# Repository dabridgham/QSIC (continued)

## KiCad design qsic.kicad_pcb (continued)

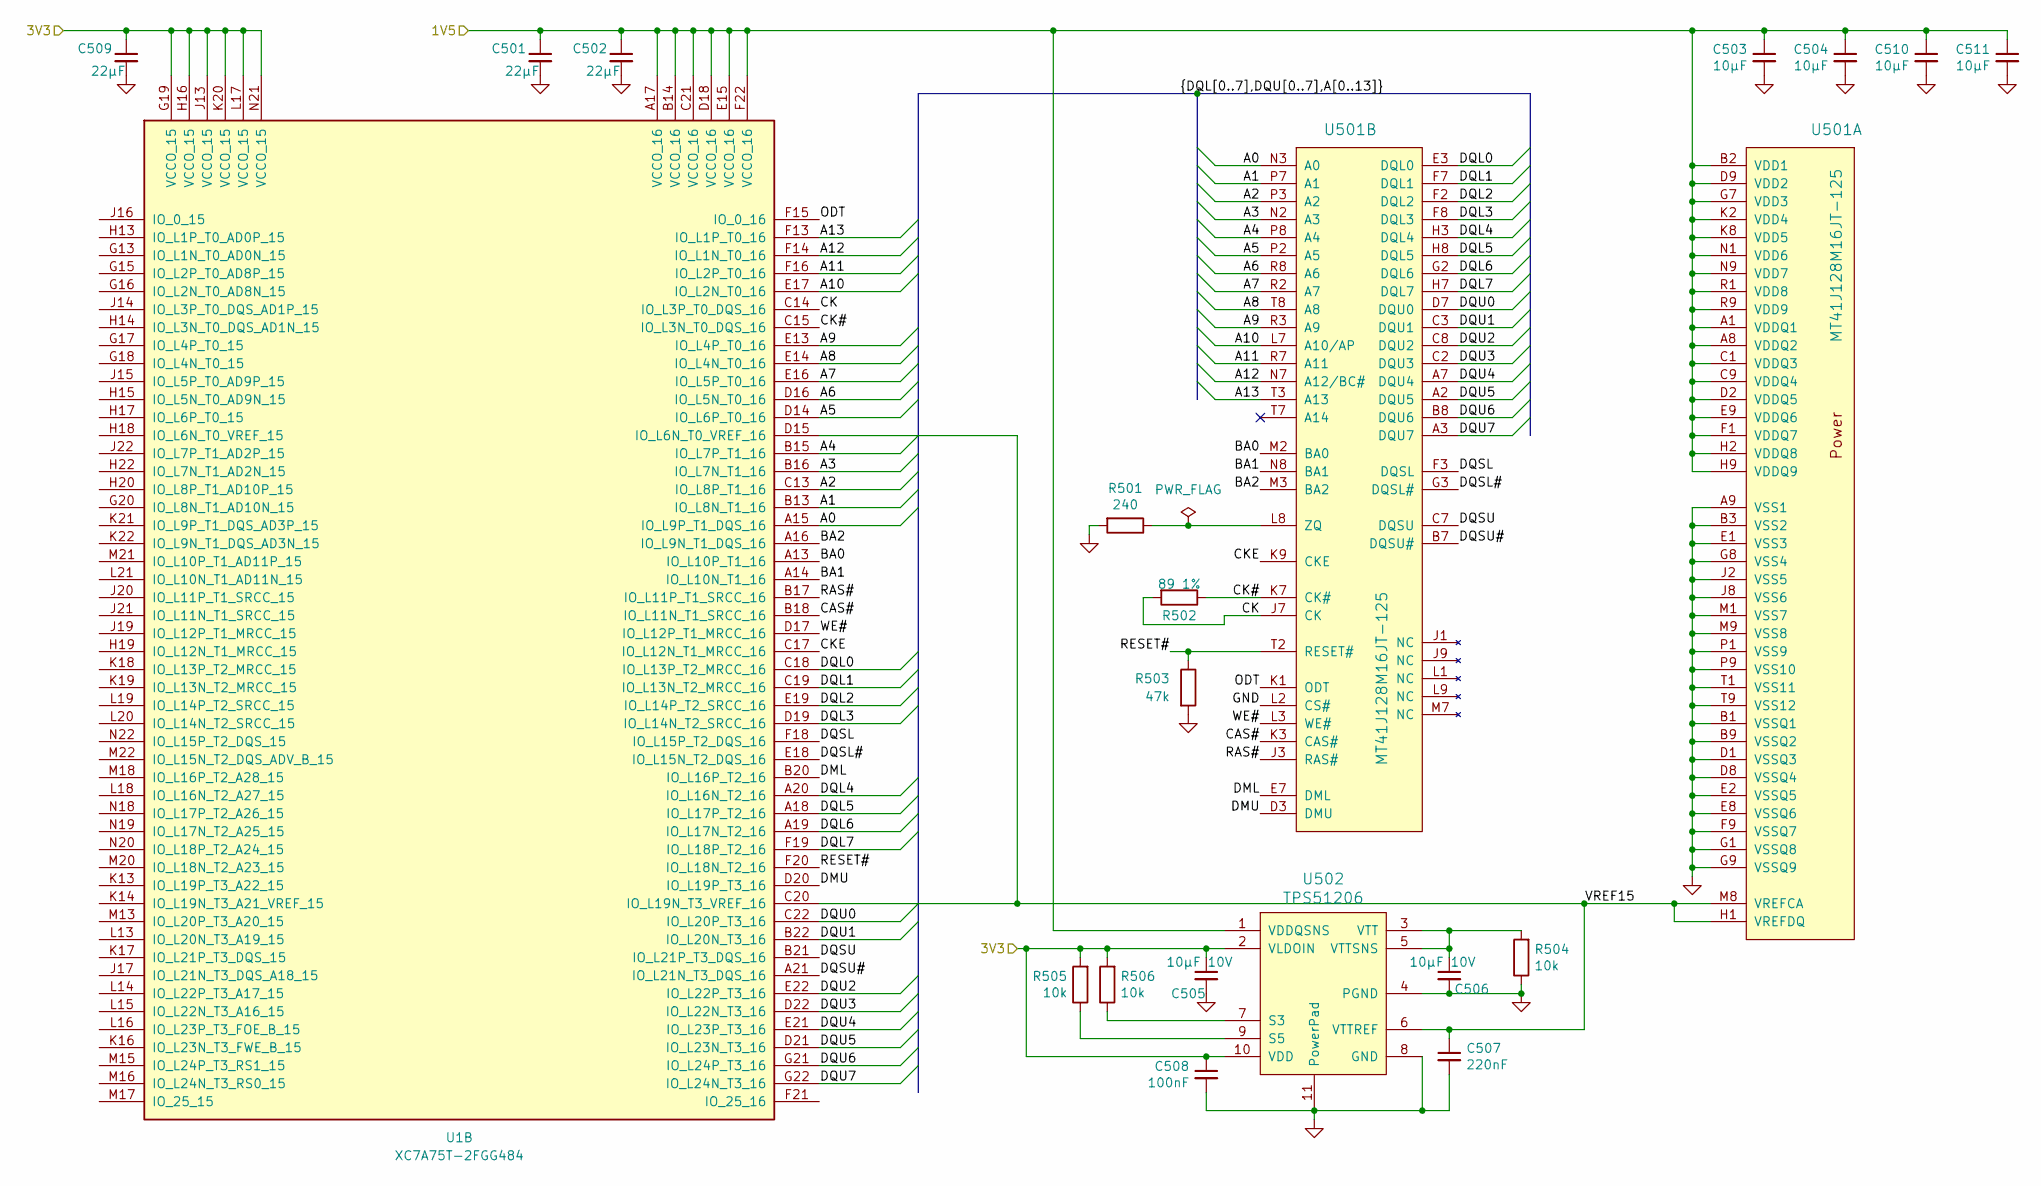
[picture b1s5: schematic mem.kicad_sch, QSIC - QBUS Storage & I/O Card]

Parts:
C501, C502, C509: 22µF; C_0603_1608Metric; MPN CL10A226MP8NUNE; JLCPCB Part C59461
C503, C504, C510, C511: 10µF; C_0603_1608Metric; MPN CL10A106MP8NNNC; JLCPCB Part C85713
C505, C506: 10µF 10V; C_0603_1608Metric; MPN CL10A106MP8NNNC; JLCPCB Part C85713
C507: 220nF; C_0603_1608Metric; MPN CL10B224KO8NNNC
C508: 100nF; C_0603_1608Metric; MPN CL10B104KO8NNNC
R501: 240; R_0603_1608Metric; MPN RC0603FR-07240RL
R502: 89 1%; R_0603_1608Metric; MPN RC0603FR-0788R7L; JLCPCB Part C273787
R503: 47k; R_0603_1608Metric; MPN RC0603FR-0747KL
R504, R505, R506: 10k; R_0603_1608Metric; MPN RC0603FR-0710KL
U1: XC7A75T-2FGG484; Xilinx_FGG484
U501: MT41J128M16JT-125; BGA-96_9.0x13.0mm_Layout2x3x16_P0.8mm; MPN MT41J128M16JT-125:K TR
U502: TPS51206; WSON-10-1EP_2x2mm_P0.4mm_EP0.9x1.5mm_ThermalVias; MPN TPS51206DSQR; JLCPCB Part C88038

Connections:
/1V5: C501.1, C502.1, C503.1, C504.1, C510.1, C511.1, U1.A17 (VCCO_16), U1.B14 (VCCO_16), U1.C21 (VCCO_16), U1.D18 (VCCO_16), U1.E15 (VCCO_16), U1.F22 (VCCO_16), U501.A1 (VDDQ1), U501.A8 (VDDQ2), U501.B2 (VDD1), U501.C1 (VDDQ3), U501.C9 (VDDQ4), U501.D2 (VDDQ5), U501.D9 (VDD2), U501.E9 (VDDQ6), U501.F1 (VDDQ7), U501.G7 (VDD3), U501.H2 (VDDQ8), U501.H9 (VDDQ9), U501.K2 (VDD4), U501.K8 (VDD5), U501.N1 (VDD6), U501.N9 (VDD7), U501.R1 (VDD8), U501.R9 (VDD9), U502.1 (VDDQSNS); also elsewhere on the board
/3V3: C505.1, C508.1, C509.1, R505.2, R506.2, U1.G19 (VCCO_15), U1.H16 (VCCO_15), U1.J13 (VCCO_15), U1.K20 (VCCO_15), U1.L17 (VCCO_15), U1.N21 (VCCO_15), U502.2 (VLDOIN), U502.10 (VDD); also elsewhere on the board
/Memory/A0: U1.A15 (IO_L9P_T1_DQS_16), U501.N3 (A0)
/Memory/A1: U1.B13 (IO_L8N_T1_16), U501.P7 (A1)
/Memory/A2: U1.C13 (IO_L8P_T1_16), U501.P3 (A2)
/Memory/A3: U1.B16 (IO_L7N_T1_16), U501.N2 (A3)
/Memory/A4: U1.B15 (IO_L7P_T1_16), U501.P8 (A4)
/Memory/A5: U1.D14 (IO_L6P_T0_16), U501.P2 (A5)
/Memory/A6: U1.D16 (IO_L5N_T0_16), U501.R8 (A6)
/Memory/A7: U1.E16 (IO_L5P_T0_16), U501.R2 (A7)
/Memory/A8: U1.E14 (IO_L4N_T0_16), U501.T8 (A8)
/Memory/A9: U1.E13 (IO_L4P_T0_16), U501.R3 (A9)
/Memory/A10: U1.E17 (IO_L2N_T0_16), U501.L7 (A10/AP)
/Memory/A11: U1.F16 (IO_L2P_T0_16), U501.R7 (A11)
/Memory/A12: U1.F14 (IO_L1N_T0_16), U501.N7 (A12/BC#)
/Memory/A13: U1.F13 (IO_L1P_T0_16), U501.T3 (A13)
/Memory/BA0: U1.A13 (IO_L10P_T1_16), U501.M2 (BA0)
/Memory/BA1: U1.A14 (IO_L10N_T1_16), U501.N8 (BA1)
/Memory/BA2: U1.A16 (IO_L9N_T1_DQS_16), U501.M3 (BA2)
/Memory/CAS#: U1.B18 (IO_L11N_T1_SRCC_16), U501.K3 (CAS#)
/Memory/CK: R502.2, U1.C14 (IO_L3P_T0_DQS_16), U501.J7 (CK)
/Memory/CK#: R502.1, U1.C15 (IO_L3N_T0_DQS_16), U501.K7 (CK#)
/Memory/CKE: U1.C17 (IO_L12N_T1_MRCC_16), U501.K9 (CKE)
/Memory/DML: U1.B20 (IO_L16P_T2_16), U501.E7 (DML)
/Memory/DMU: U1.D20 (IO_L19P_T3_16), U501.D3 (DMU)
/Memory/DQL0: U1.C18 (IO_L13P_T2_MRCC_16), U501.E3 (DQL0)
/Memory/DQL1: U1.C19 (IO_L13N_T2_MRCC_16), U501.F7 (DQL1)
/Memory/DQL2: U1.E19 (IO_L14P_T2_SRCC_16), U501.F2 (DQL2)
/Memory/DQL3: U1.D19 (IO_L14N_T2_SRCC_16), U501.F8 (DQL3)
/Memory/DQL4: U1.A20 (IO_L16N_T2_16), U501.H3 (DQL4)
/Memory/DQL5: U1.A18 (IO_L17P_T2_16), U501.H8 (DQL5)
/Memory/DQL6: U1.A19 (IO_L17N_T2_16), U501.G2 (DQL6)
/Memory/DQL7: U1.F19 (IO_L18P_T2_16), U501.H7 (DQL7)
/Memory/DQSL: U1.F18 (IO_L15P_T2_DQS_16), U501.F3 (DQSL)
/Memory/DQSL#: U1.E18 (IO_L15N_T2_DQS_16), U501.G3 (DQSL#)
/Memory/DQSU: U1.B21 (IO_L21P_T3_DQS_16), U501.C7 (DQSU)
/Memory/DQSU#: U1.A21 (IO_L21N_T3_DQS_16), U501.B7 (DQSU#)
/Memory/DQU0: U1.C22 (IO_L20P_T3_16), U501.D7 (DQU0)
/Memory/DQU1: U1.B22 (IO_L20N_T3_16), U501.C3 (DQU1)
/Memory/DQU2: U1.E22 (IO_L22P_T3_16), U501.C8 (DQU2)
/Memory/DQU3: U1.D22 (IO_L22N_T3_16), U501.C2 (DQU3)
/Memory/DQU4: U1.E21 (IO_L23P_T3_16), U501.A7 (DQU4)
/Memory/DQU5: U1.D21 (IO_L23N_T3_16), U501.A2 (DQU5)
/Memory/DQU6: U1.G21 (IO_L24P_T3_16), U501.B8 (DQU6)
/Memory/DQU7: U1.G22 (IO_L24N_T3_16), U501.A3 (DQU7)
/Memory/ODT: U1.F15 (IO_0_16), U501.K1 (ODT)
/Memory/RAS#: U1.B17 (IO_L11P_T1_SRCC_16), U501.J3 (RAS#)
/Memory/RESET#: R503.1, U1.F20 (IO_L18N_T2_16), U501.T2 (RESET#)
/Memory/VREF15: C507.1, U1.C20 (IO_L19N_T3_VREF_16), U1.D15 (IO_L6N_T0_VREF_16), U501.H1 (VREFDQ), U501.M8 (VREFCA), U502.6 (VTTREF)
/Memory/WE#: U1.D17 (IO_L12P_T1_MRCC_16), U501.L3 (WE#)
GND: C501.2, C502.2, C503.2, C504.2, C505.2, C506.2, C507.2, C508.2, C509.2, C510.2, C511.2, R501.2, R503.2, R504.1, U501.A9 (VSS1), U501.B1 (VSSQ1), U501.B3 (VSS2), U501.B9 (VSSQ2), U501.D1 (VSSQ3), U501.D8 (VSSQ4), U501.E1 (VSS3), U501.E2 (VSSQ5), U501.E8 (VSSQ6), U501.F9 (VSSQ7), U501.G1 (VSSQ8), U501.G8 (VSS4), U501.G9 (VSSQ9), U501.J2 (VSS5), U501.J8 (VSS6), U501.L2 (CS#), U501.M1 (VSS7), U501.M9 (VSS8), U501.P1 (VSS9), U501.P9 (VSS10), U501.T1 (VSS11), U501.T9 (VSS12), U502.4 (PGND), U502.8 (GND), U502.11 (PowerPad); also elsewhere on the board
unnamed: R501.1, U501.L8 (ZQ)
unnamed: R506.1, U502.7 (S3)
unnamed: R505.1, U502.9 (S5)
unnamed: C506.1, R504.2, U502.3 (VTT), U502.5 (VTTSNS)

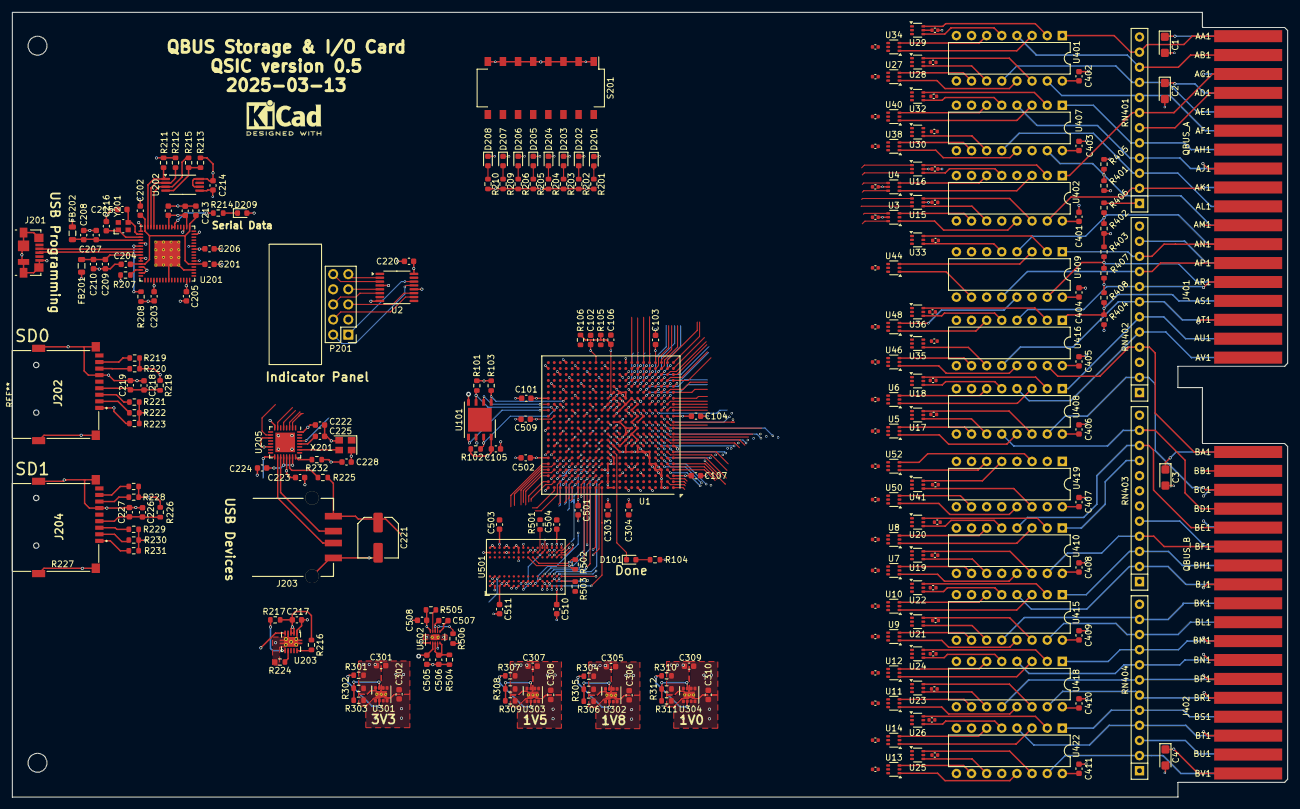
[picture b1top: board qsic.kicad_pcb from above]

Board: 6 copper layers, 214.1 x 131.7 mm, 268 parts (0 on the bottom side), 382 nets.

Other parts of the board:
LOGO101: KiCad Logo; KiCad-Logo2_5mm_SilkScreen

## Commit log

2024-01-06 The initial commit of the files after rearranging the git structure to separate out the hardware projects from the software ones. At this point, the QSIC pcb design is largely done; it just hasn't be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
2024-01-06 Added links
2024-01-06 corrected URL
2025-03-12 Updated to KiCad 9, fiddled around with 3d model of the handle, and removed unused pins on the QBUS connector.
2025-04-08 Added the JLC production files and directory
2025-04-08 Cleaned up the directory and renamed files. Also all the changes to move from the 324 package to the 484 (not yet completed).
2025-04-08 Cleaned up the directory and renamed files. Also converted from the 324 package on the FPGA to the 484 package. That conversion is still in-progress.
2025-04-12 Switched the level converters to 74HCT2G04 and 75LVC2G04. Still need to remap the FPGA pins to the signal odering.
2025-04-12 tiny change of a label
